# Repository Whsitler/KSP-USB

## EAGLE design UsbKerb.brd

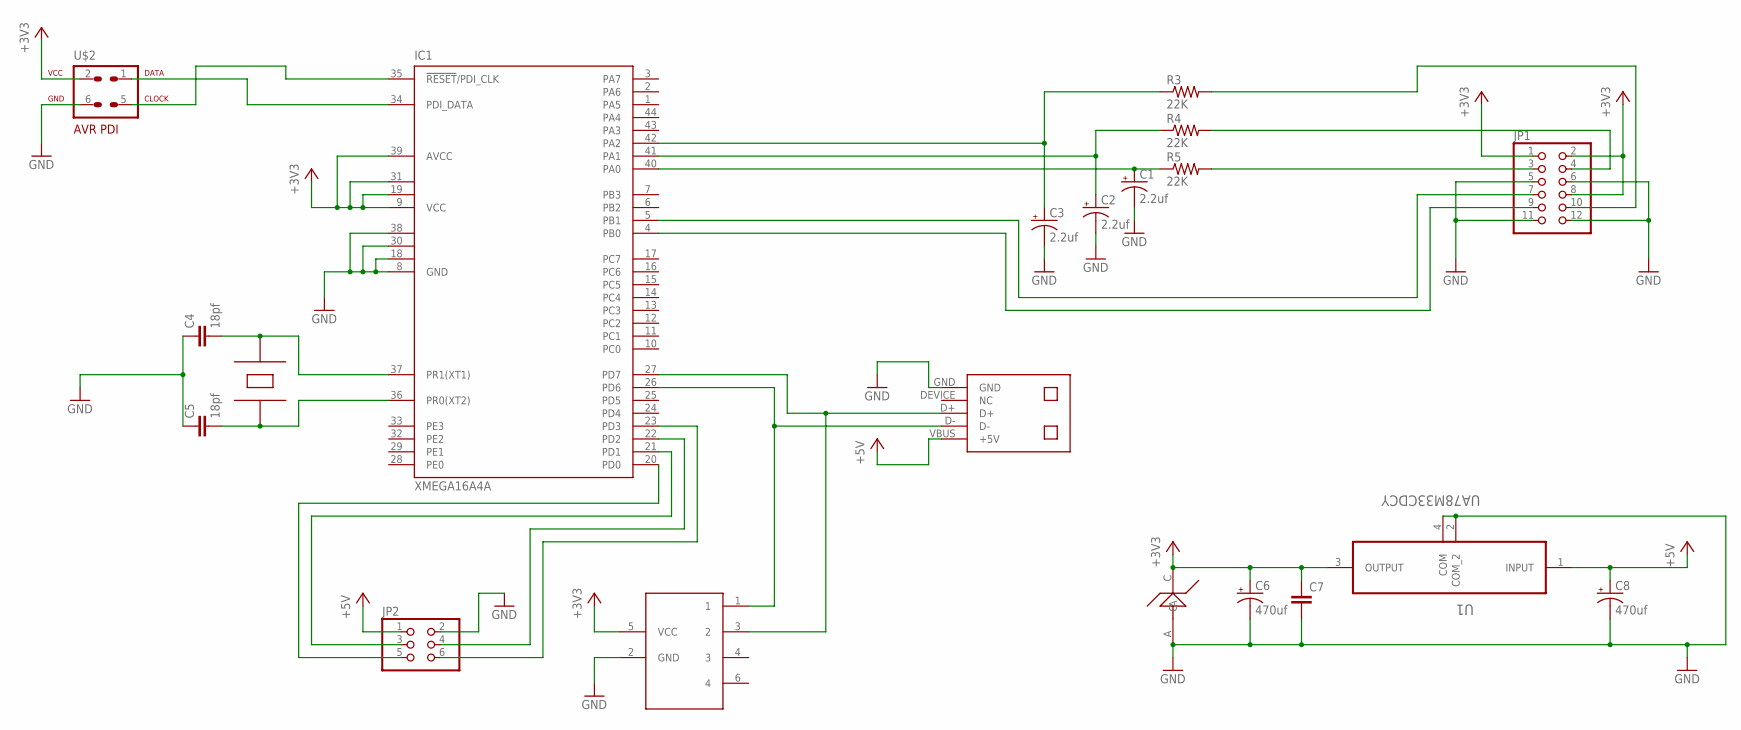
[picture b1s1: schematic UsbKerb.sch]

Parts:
C1, C2, C3: 2.2uf; PANASONIC_B
C4, C5: 18pf; C0805K
C6, C8: 470uf; PANASONIC_G
C7: C-EUC1206K; C1206K
IC1: XMEGA16A4A; TQFP44
JP1: PINHD-2X6; 2X06
JP2: PINHD-2X3; 2X03
R3, R4, R5: 22K; R0805W
U1: UA78M33CDCY; SOT230P700X180-4N
U2: 3.3TVS; SOT23-6L
U$1: USB-MINI
U$2: AVR-PDIVERT; AVR-ISP-6
U$3: TVS; DO214AC
U$4: 12MHZ

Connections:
+3V3: C6.+, C7.1, IC1.9 (VCC), IC1.19 (VCC1), IC1.31 (VCC2), IC1.39 (AVCC), JP1.1, JP1.2, JP1.8, U1.3 (OUTPUT), U2.5 (VCC), U$2.2, U$3.C
+5V: C8.+, JP2.1, U1.1 (INPUT), U$1.VBUS (+5V)
GND: C1.-, C2.-, C3.-, C4.1, C5.1, C6.-, C7.2, C8.-, IC1.8 (GND), IC1.18 (GND1), IC1.30 (GND2), IC1.38 (GND3), JP1.5, JP1.6, JP1.11, JP1.12, JP2.2, U1.2 (COM_2), U1.4 (COM), U2.2 (GND), U$1.GND, U$2.6, U$3.A
unnamed: C1.+, IC1.40 (PA0), R5.1
unnamed: IC1.27 (PD7), U2.3 (2), U$1.D+
unnamed: IC1.34 (PDI_DATA), U$2.1
unnamed: IC1.26 (PD6), U2.1, U$1.D-
unnamed: C2.+, IC1.41 (PA1), R4.1
unnamed: C3.+, IC1.42 (PA2), R3.1
unnamed: IC1.35 (!RESET!/PDI_CLK), U$2.5
unnamed: JP1.10, R3.2
unnamed: JP1.4, R4.2
unnamed: JP1.3, R5.2
unnamed: IC1.4 (PB0), JP1.9
unnamed: IC1.5 (PB1), JP1.7
unnamed: C4.2, IC1.37 (PR1(XT1)), U$4.P$1
unnamed: C5.2, IC1.36 (PR0(XT2)), U$4.P$2
unnamed: IC1.22 (PD2), JP2.4
unnamed: IC1.20 (PD0), JP2.5
unnamed: IC1.21 (PD1), JP2.3
unnamed: IC1.23 (PD3), JP2.6

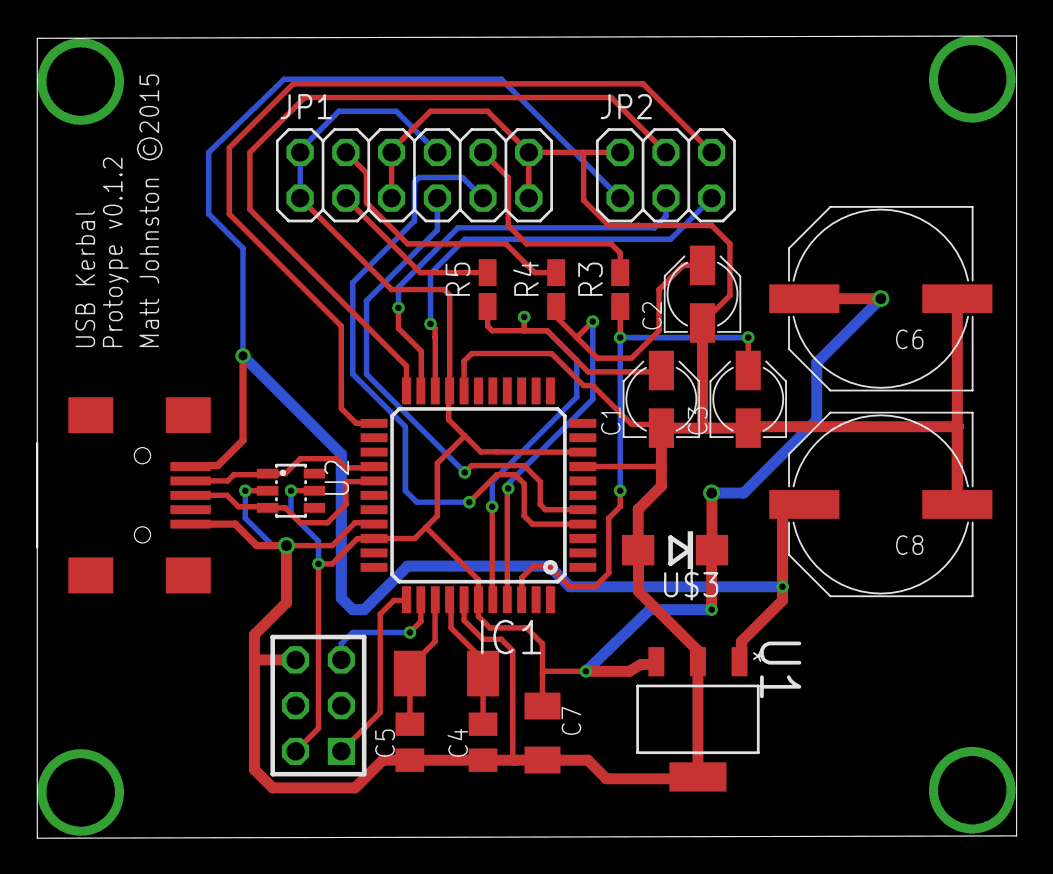
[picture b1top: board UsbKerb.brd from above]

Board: 2 copper layers, 54.4 x 44.4 mm, 20 parts (0 on the bottom side), 21 nets.

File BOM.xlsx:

IC1 | XMEGA16A4A | 44pin TQFP
R3 | 22kohm | 805
R4 | 22kohm | 805
R5 | 22kohm | 805
C1 | 2.2uf | Panasonic B
C2 | 2.2uf | Panasonic B
C3 | 2.2uf | Panasonic B
C4 | 18pf | 805
C5 | 18pf | 805
C6 | 470uf | Panasonic G
C7 | 100pf | 1206
C8 | 470uf | Panasonic G
U4 | 12mhz
U1 | 3.3V | SOT23 | UA78M33CDCY
U2 |  | SOT23-6L

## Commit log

2015-03-26 :space_invader: Added .gitattributes & .gitignore files
2015-03-26 setup
2015-03-27 more footprints added
2015-03-31 Replaced out of stock tvs foot print
2015-03-31 fixed power rails
2015-04-01 board Layout complete?
2015-04-04 created panel layout and several footprints
2015-04-25 Corrected board layout for voltage and regulator footprint
2015-12-18 Swapped USB Pads for USB Mini connector
2015-12-25 Added BOM

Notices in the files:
UsbKerb.brd:
Matt Johnston ©2015
